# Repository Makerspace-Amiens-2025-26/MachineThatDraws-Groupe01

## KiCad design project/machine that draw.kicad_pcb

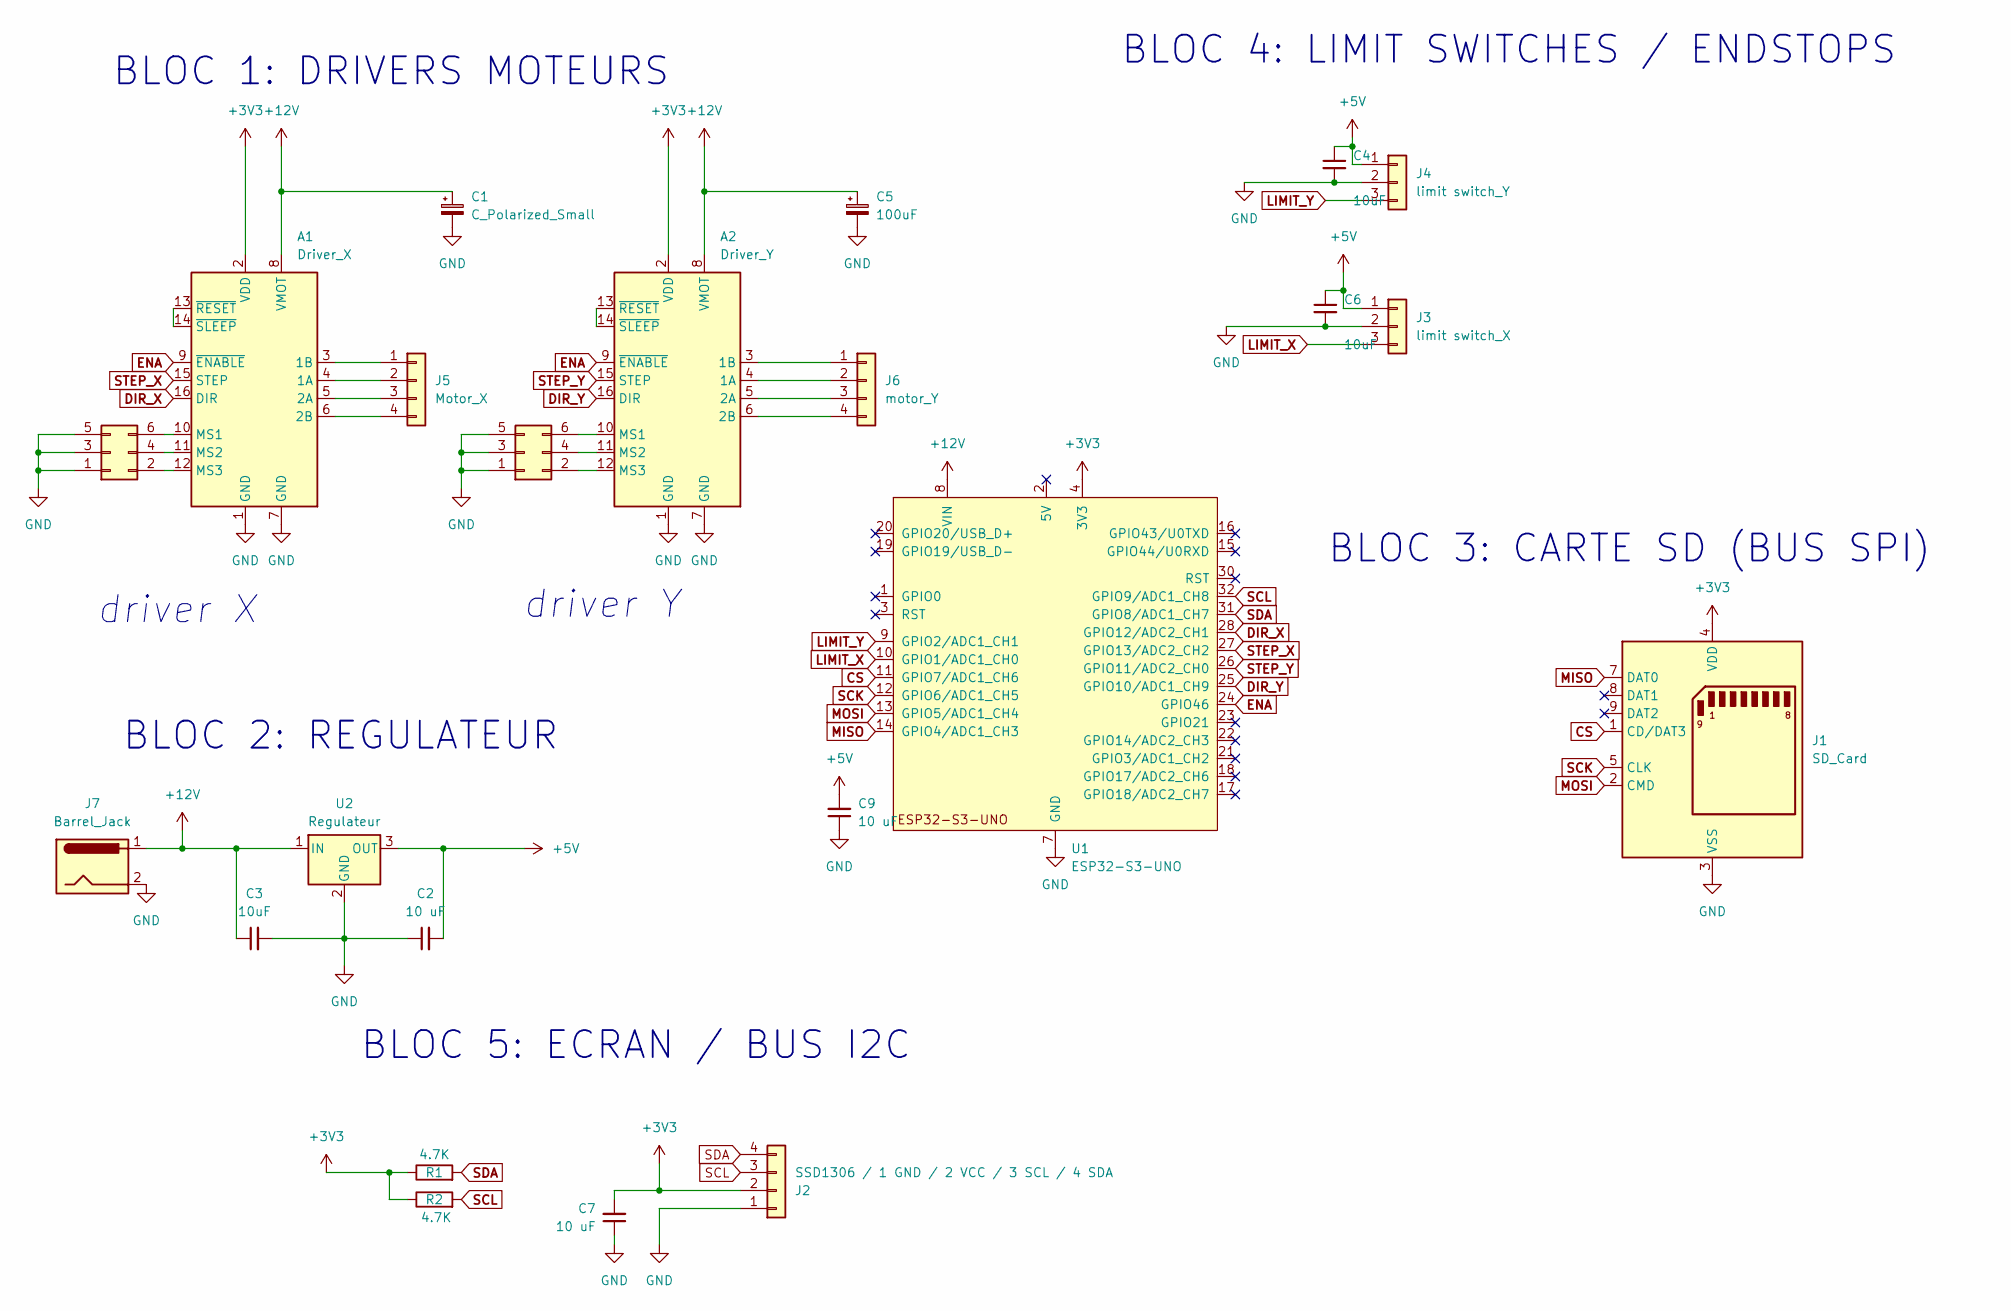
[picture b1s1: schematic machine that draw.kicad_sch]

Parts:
A1: Driver_X; Pololu_Breakout-16_15.2x20.3mm
A2: Driver_Y; Pololu_Breakout-16_15.2x20.3mm
C1: C_Polarized_Small; CP_Radial_D8.0mm_P3.50mm
C2: 10 uF; C_1206
C3, C6: 10uF; C_1206
C4: 10uF; C_1206_3216Metric_Pad1.33x1.80mm_HandSolder
C5: 100uF; CP_Radial_D8.0mm_P3.50mm
C7, C9: 10 uF; C_1206_3216Metric_Pad1.33x1.80mm_HandSolder
J1: SD_Card; SD_Hirose_DM1AA_SF_PEJ82
J2: SSD1306 / 1 GND / 2 VCC / 3 SCL / 4 SDA; PinHeader_1x04_P2.54mm_Vertical
J3: limit switch_X; PinHeader_1x03_P2.54mm_Vertical
J4: limit switch_Y; PinHeader_1x03_P2.54mm_Vertical
J5: Motor_X; PinHeader_1x04_P2.54mm_Vertical
J6: motor_Y; PinHeader_1x04_P2.54mm_Vertical
J7: Barrel_Jack; BarrelJack_Horizontal
J8, J9: Conn_02x03_Odd_Even; PinHeader_2x03_P2.54mm_Vertical
R1, R2: 4.7K; R_1206
U1: ESP32-S3-UNO; ESP_S3_UNO
U2: Regulateur; Converter_DCDC_RECOM_R-78E-0.5_THT

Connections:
+3V3: A1.2 (VDD), A2.2 (VDD), C7.2, J1.4 (VDD), J2.2, R1.1, R2.1, U1.4 (3V3)
+5V: C2.2, C4.1, C6.1, C9.2, J3.1, J4.1, U2.3 (OUT)
+12V: A1.8 (VMOT), A2.8 (VMOT), C1.1, C3.1, C5.1, J7.1, U1.8 (VIN), U2.1 (IN); also elsewhere on the board
CS: J1.1 (CD/DAT3), U1.11 (GPIO7/ADC1_CH6)
DIR_X: A1.16 (DIR), U1.28 (GPIO12/ADC2_CH1)
DIR_Y: A2.16 (DIR), U1.25 (GPIO10/ADC1_CH9)
ENA: A1.9 (~ENABLE), A2.9 (~ENABLE), U1.24 (GPIO46)
GND: A1.1 (GND), A1.7 (GND), A2.1 (GND), A2.7 (GND), C1.2, C2.1, C3.2, C4.2, C5.2, C6.2, C7.1, C9.1, J1.3 (VSS), J1.6 (VSS), J2.1, J3.2, J4.2, J7.2, J8.1, J8.3, J8.5, J9.1, J9.3, J9.5, U1.6 (GND), U1.7 (GND), U1.29 (GND), U2.2 (GND)
LIMIT_X: J3.3, U1.10 (GPIO1/ADC1_CH0)
LIMIT_Y: J4.3, U1.9 (GPIO2/ADC1_CH1)
MISO: J1.7 (DAT0), U1.14 (GPIO4/ADC1_CH3)
MOSI: J1.2 (CMD), U1.13 (GPIO5/ADC1_CH4)
unnamed: A1.4 (1A), J5.2
unnamed: A1.3 (1B), J5.1
unnamed: A1.5 (2A), J5.3
unnamed: A1.6 (2B), J5.4
unnamed: A1.10 (MS1), J9.6
unnamed: A1.11 (MS2), J9.4
unnamed: A1.12 (MS3), J9.2
unnamed: A1.13 (~RESET), A1.14 (~SLEEP)
unnamed: A2.4 (1A), J6.2
unnamed: A2.3 (1B), J6.1
unnamed: A2.5 (2A), J6.3
unnamed: A2.6 (2B), J6.4
unnamed: A2.10 (MS1), J8.6
unnamed: A2.11 (MS2), J8.4
unnamed: A2.12 (MS3), J8.2
unnamed: A2.13 (~RESET), A2.14 (~SLEEP)
SCK: J1.5 (CLK), U1.12 (GPIO6/ADC1_CH5)
SCL: J2.3, R2.2, U1.32 (GPIO9/ADC1_CH8)
SDA: J2.4, R1.2, U1.31 (GPIO8/ADC1_CH7)
STEP_X: A1.15 (STEP), U1.27 (GPIO13/ADC2_CH2)
STEP_Y: A2.15 (STEP), U1.26 (GPIO11/ADC2_CH0)

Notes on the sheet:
BLOC 3: CARTE SD (BUS SPI)
BLOC 1: DRIVERS MOTEURS
BLOC 2: REGULATEUR
BLOC 4: LIMIT SWITCHES / ENDSTOPS
BLOC 5: ECRAN / BUS I2C
driver X
driver Y

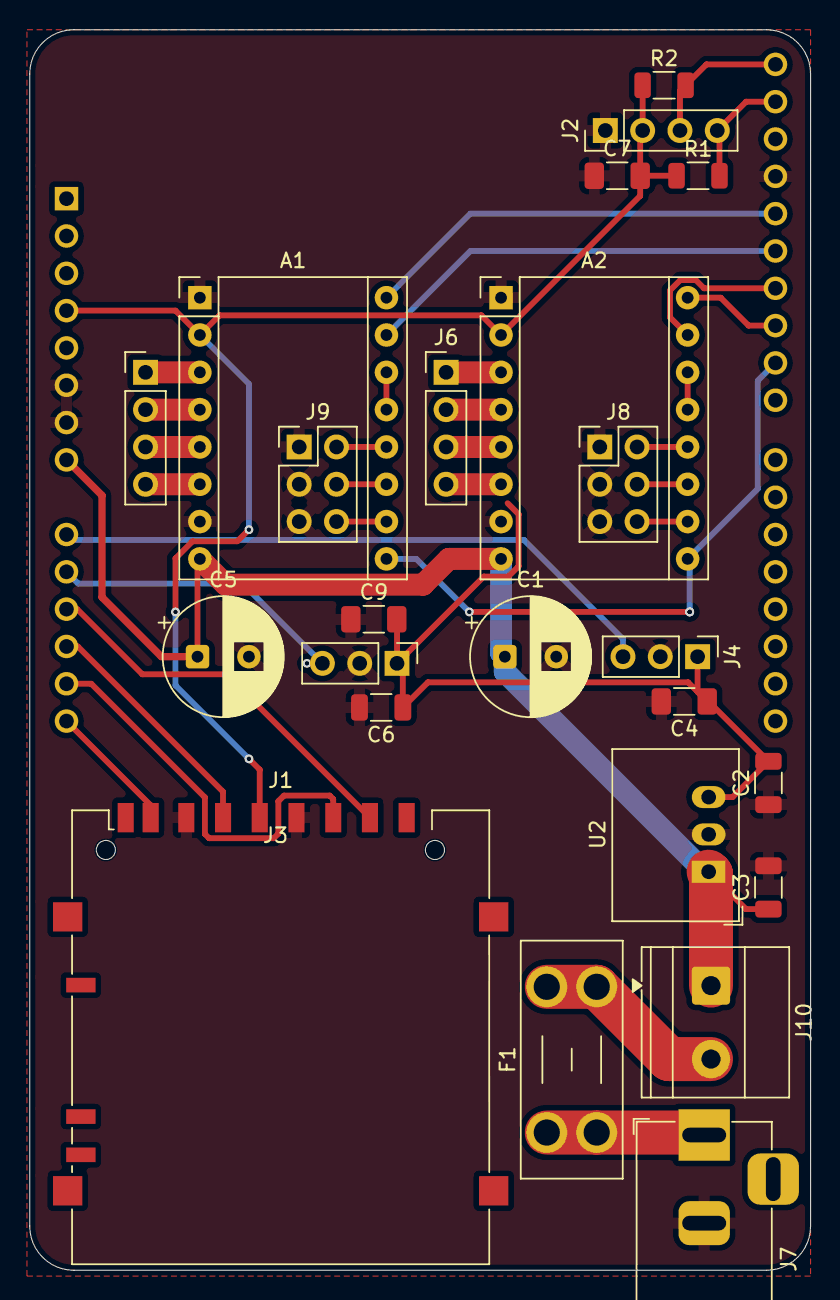
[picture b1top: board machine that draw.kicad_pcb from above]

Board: 2 copper layers, 53.1 x 84.4 mm, 25 parts (0 on the bottom side), 34 nets.

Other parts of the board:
F1: Fuse; Fuseholder_Blade_Mini_Keystone_3568
J10: Screw_Terminal_01x02; TerminalBlock_Phoenix_MKDS-1,5-2_1x02_P5.00mm_Horizontal

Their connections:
+12V: J10.1; also elsewhere on the board
unnamed: F1.2, J10.2

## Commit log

2026-03-20 Added ECAD files
2026-03-20 Added test line to README
2026-03-20 Removed test lines in README
2026-03-20 Added a capacitor
2026-03-20 Removed test
2026-03-20 3D onshape.md
2026-03-25 schematics
2026-04-10 Created PCB file
2026-04-10 PCB composant placed
2026-04-20 EDITED PCB
2026-04-22 finalisation pcb
2026-04-24 Validation PCB pour production
    Nota : re-génération de plan de masse
2026-04-27 fix wiring problems
2026-06-05 poster.jpg
2026-06-05 Rename White Black Bold Minimalist Furniture Catalog Poster.png to poster.png
2026-06-05 Rename poster.png to poster.jpg
2026-06-06 Rename premiers-pas.md to _premiers-pas.md
2026-06-06 Rename introduction_git_github.md to _introduction_git_github.md
2026-06-06 Rename markdown_cheatsheet.md to _markdown_cheatsheet.md
2026-06-06 Rename modifier_mon_site.md to _modifier_mon_site.md
2026-06-06 Rename modifier_mon_site_avance.md to _modifier_mon_site_avance.md
2026-06-06 Rename pcb face bleue.png to pcbfacebleue.png
2026-06-06 Rename pcb face rouge.png to pcbfacerouge.png
2026-06-06 Rename etape_1.md to _etape_1.md
2026-06-06 Rename etape_2.md to _etape_2.md
2026-06-06 Rename etapes.md to _etapes.md
2026-06-06 Rename _etape_1.md to etape_1.md
2026-06-06 Rename _etapes.md to etapes.md
2026-06-06 Rename _etape_2.md to etape_2.md
2026-06-08 Rename 8mb.video-eFq-Gn6Ujeo0.mp4 to vidéo.mp4
